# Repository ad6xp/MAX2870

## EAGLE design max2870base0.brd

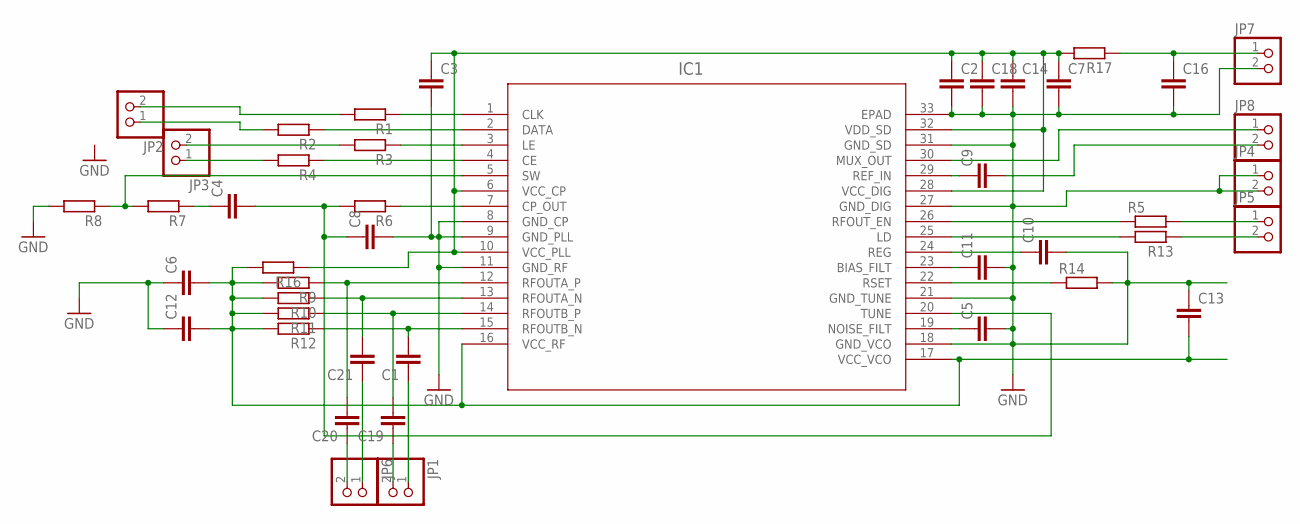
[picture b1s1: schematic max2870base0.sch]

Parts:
C1, C2, C3, C4, C5, C6, C7, C8, C9, C10, C11, C12, C19, C20, C21: C-EUC0805; C0805
C13, C14, C16: C-EUC1206; C1206
C18: C-EUC1808; C1808
IC1: MAX2870ETJ+; 21-0140L_T3255-5
JP1, JP2, JP3, JP4, JP5, JP6, JP7, JP8: PINHD-1X2; 1X02
R1, R2, R3, R4, R5, R6, R7, R8, R13, R14, R17: R-EU_R0805; R0805
R9, R10, R11, R12: R-EU_M0805; M0805
R16: R-EU_R1206; R1206

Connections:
CE: JP3.1, R4.2
CLK: JP2.2, R1.2
DATA: JP2.1, R2.2
GND: C2.2, C3.2, C5.2, C6.1, C7.2, C8.2, C10.2, C11.2, C12.1, C13.1, C14.2, C16.2, C18.2, IC1.8 (GND_CP), IC1.9 (GND_PLL), IC1.11 (GND_RF), IC1.18 (GND_VCO), IC1.21 (GND_TUNE), IC1.27 (GND_DIG), IC1.31 (GND_SD), IC1.33 (EPAD), JP4.1, JP4.2, JP7.2, R8.2, R14.2
LD: JP5.2, R13.1
LE: JP3.2, R3.2
MUX: IC1.30 (MUX_OUT), JP8.1
unnamed: IC1.7 (CP_OUT), R6.1
unnamed: IC1.1 (CLK), R1.1
unnamed: IC1.5 (SW), R7.2, R8.1
unnamed: IC1.3 (LE), R3.1
unnamed: C1.1, JP1.1
unnamed: C4.1, R7.1
unnamed: IC1.2 (DATA), R2.1
unnamed: IC1.4 (CE), R4.1
unnamed: C20.2, IC1.12 (RFOUTA_P), R9.1
unnamed: C21.2, IC1.13 (RFOUTA_N), R10.1
unnamed: C1.2, IC1.15 (RFOUTB_N), R12.1
unnamed: C19.2, IC1.14 (RFOUTB_P), R11.1
unnamed: C19.1, JP1.2
unnamed: C5.1, IC1.19 (NOISE_FILT)
unnamed: IC1.22 (RSET), R14.1
unnamed: C11.1, IC1.23 (BIAS_FILT)
unnamed: C10.1, IC1.24 (REG)
unnamed: C9.1, IC1.29 (REF_IN)
unnamed: C9.2, JP8.2
unnamed: IC1.26 (RFOUT_EN), R5.1
unnamed: IC1.25 (LD), R13.2
unnamed: C21.1, JP6.1
unnamed: C20.1, JP6.2
unnamed: JP5.1, R5.2
unnamed: C16.1, JP7.1, R17.1
TUNE: C4.2, C8.1, IC1.20 (TUNE), R6.2
VCCDIG: C2.1, C3.1, C7.1, C14.1, C18.1, IC1.6 (VCC_CP), IC1.10 (VCC_PLL), IC1.28 (VCC_DIG), IC1.32 (VDD_SD), R16.1, R17.2
VCCRF: C6.2, C12.2, C13.2, IC1.16 (VCC_RF), IC1.17 (VCC_VCO), R9.2, R10.2, R11.2, R12.2, R16.2

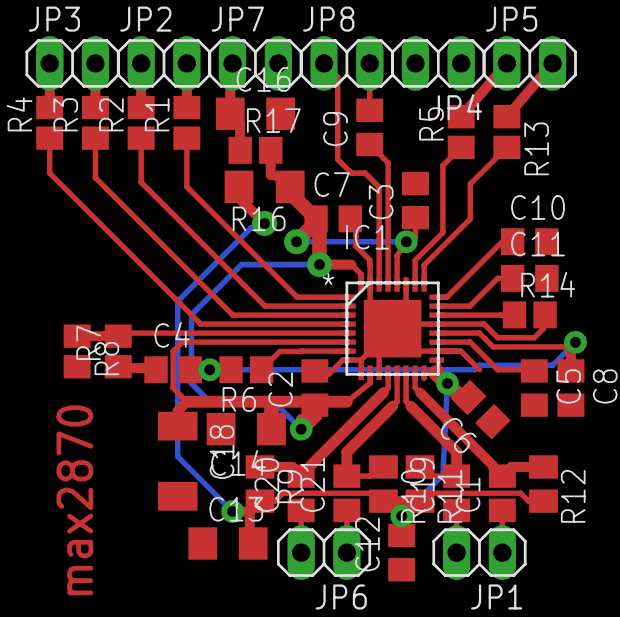
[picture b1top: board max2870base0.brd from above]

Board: 2 copper layers, 44 parts (0 on the bottom side), 35 nets.
